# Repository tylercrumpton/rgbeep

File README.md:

# rgbeep
An ESP-powered RGB-lit jumbo button using APA102 LEDs.

![pcb-top]![pcb-bottom]

## Overview
The **RGBeep** is a large, colorful WiFi button made using the parts from an off-the-shelf "tap light".
It was inspired by [todbot's CrashSpace BigButton][todbot] that uses the same components. I loved the design,
but wanted to use APA102 RGB LEDs instead WS2182s, remove the "sacrificial Neopixel", and play with the mechanics a little bit.

On board, there are 16 APA102 SPI-controllable RGB LEDs, four pushbuttons, and a socket for either a Wemos D1 Mini ESP8266 module
or a [Synapse-powered S1 Mini][s1].

The diffuser insert is optional, but helps to hide the pixels underneath the dome. It is meant to be installed between 
the PCB and the dome with the "fins" oriented downwards, torward the PCB. White filament is recommended. 
The model was designed/printed/tested with an FDM printer at .2mm layer height.

## Operation
The **RGBeep**'s D1 Mini or S1 Mini module communicate with the APA102 LEDs via SPI, and the pushbuttons are connected to GPIO pins.
The pin mappings are as follows:

| Description | Module Pin |
|-------------|------------|
| APA102 CLK  | D5         |
| APA102 DATA | D7         |
| Switch SW1  | D1         |
| Switch SW2  | D2         |
| Switch SW3  | D3         |
| Switch SW4  | D4         |

[pcb-top]: https://cloud.githubusercontent.com/assets/1317406/22604399/045c0e30-ea11-11e6-9dd1-bee5b901c55e.png
[pcb-bottom]: https://cloud.githubusercontent.com/assets/1317406/22604385/fb816bde-ea10-11e6-9f9d-aa37f6f3053a.png
[todbot]: https://todbot.com/blog/2017/01/12/crashspace-bigbutton-w-esp8266/
[s1]: https://github.com/tylercrumpton/s1-mini

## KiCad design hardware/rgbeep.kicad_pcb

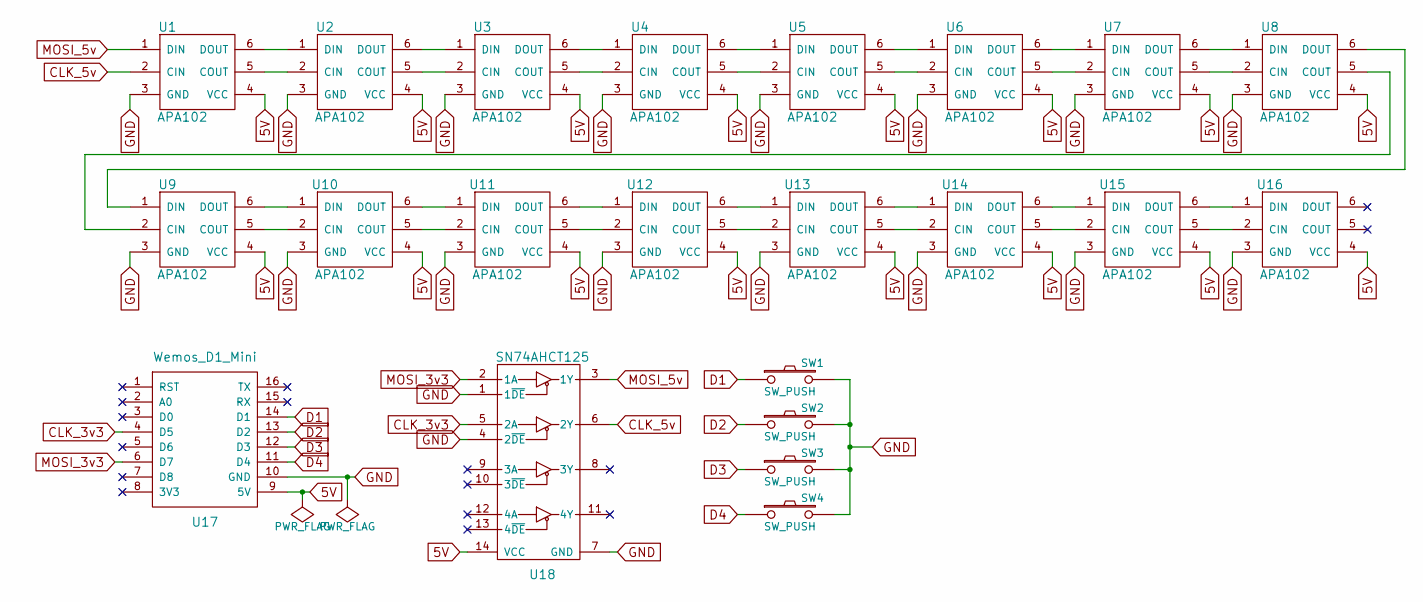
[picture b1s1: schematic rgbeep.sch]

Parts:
SW1, SW2, SW3, SW4: SW_PUSH; 6x6mm_pushbutton
U1, U2, U3, U4, U5, U6, U7, U8, U9, U10, U11, U12, U13, U14, U15, U16: APA102
U17: Wemos_D1_Mini; D1_mini
U18: SN74AHCT125; SOIC-14_3.9x8.7mm_Pitch1.27mm

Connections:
5V: U1.4 (VCC), U2.4 (VCC), U3.4 (VCC), U4.4 (VCC), U5.4 (VCC), U6.4 (VCC), U7.4 (VCC), U8.4 (VCC), U9.4 (VCC), U10.4 (VCC), U11.4 (VCC), U12.4 (VCC), U13.4 (VCC), U14.4 (VCC), U15.4 (VCC), U16.4 (VCC), U17.9 (5V), U18.14 (VCC)
CLK_3v3: U17.4 (D5), U18.5 (2A)
CLK_5v: U1.2 (CIN), U18.6 (2Y)
D1: SW1.1, U17.14 (D1)
D2: SW2.1, U17.13 (D2)
D3: SW3.1, U17.12 (D3)
D4: SW4.1, U17.11 (D4)
GND: SW1.2, SW2.2, SW3.2, SW4.2, U1.3 (GND), U2.3 (GND), U3.3 (GND), U4.3 (GND), U5.3 (GND), U6.3 (GND), U7.3 (GND), U8.3 (GND), U9.3 (GND), U10.3 (GND), U11.3 (GND), U12.3 (GND), U13.3 (GND), U14.3 (GND), U15.3 (GND), U16.3 (GND), U17.10 (GND), U18.1 (1~DE), U18.4 (2~DE), U18.7 (GND)
MOSI_3v3: U17.6 (D7), U18.2 (1A)
MOSI_5v: U1.1 (DIN), U18.3 (1Y)
unnamed: U1.5 (COUT), U2.2 (CIN)
unnamed: U1.6 (DOUT), U2.1 (DIN)
unnamed: U2.5 (COUT), U3.2 (CIN)
unnamed: U2.6 (DOUT), U3.1 (DIN)
unnamed: U3.5 (COUT), U4.2 (CIN)
unnamed: U3.6 (DOUT), U4.1 (DIN)
unnamed: U4.5 (COUT), U5.2 (CIN)
unnamed: U4.6 (DOUT), U5.1 (DIN)
unnamed: U5.5 (COUT), U6.2 (CIN)
unnamed: U5.6 (DOUT), U6.1 (DIN)
unnamed: U6.5 (COUT), U7.2 (CIN)
unnamed: U6.6 (DOUT), U7.1 (DIN)
unnamed: U7.5 (COUT), U8.2 (CIN)
unnamed: U7.6 (DOUT), U8.1 (DIN)
unnamed: U8.5 (COUT), U9.2 (CIN)
unnamed: U8.6 (DOUT), U9.1 (DIN)
unnamed: U9.6 (DOUT), U10.1 (DIN)
unnamed: U9.5 (COUT), U10.2 (CIN)
unnamed: U10.5 (COUT), U11.2 (CIN)
unnamed: U10.6 (DOUT), U11.1 (DIN)
unnamed: U11.5 (COUT), U12.2 (CIN)
unnamed: U11.6 (DOUT), U12.1 (DIN)
unnamed: U12.5 (COUT), U13.2 (CIN)
unnamed: U12.6 (DOUT), U13.1 (DIN)
unnamed: U13.5 (COUT), U14.2 (CIN)
unnamed: U13.6 (DOUT), U14.1 (DIN)
unnamed: U14.5 (COUT), U15.2 (CIN)
unnamed: U14.6 (DOUT), U15.1 (DIN)
unnamed: U15.5 (COUT), U16.2 (CIN)
unnamed: U15.6 (DOUT), U16.1 (DIN)

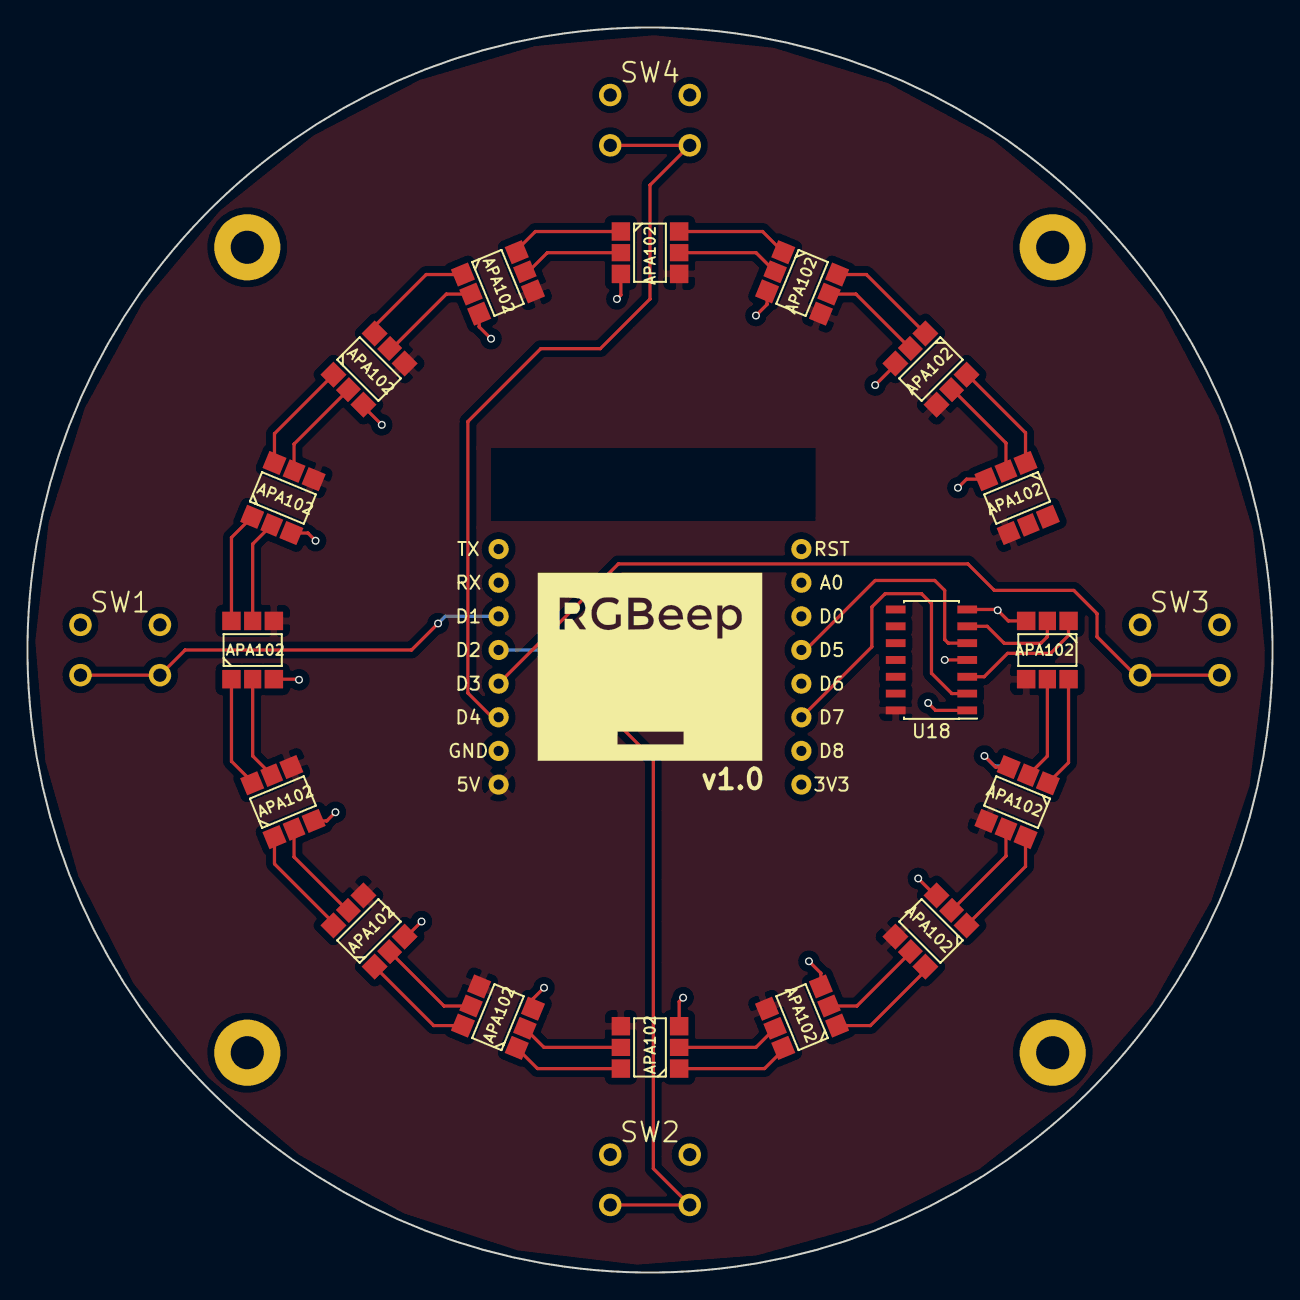
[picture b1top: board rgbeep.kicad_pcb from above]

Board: 2 copper layers, 94.0 x 94.0 mm, 22 parts (1 on the bottom side), 40 nets.

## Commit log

2017-01-29 Add KiCad project template.
2017-01-29 Update CrumpSchemes to get level shifter.
2017-01-29 Add schematic capture.
2017-01-29 Select footprints for parts.
2017-02-01 Route v1.0 board.
2017-02-03 Set plot settings.
2017-02-08 Add all the info to README.
2017-03-02 Fix DATA pin number.
2019-12-22 3D printable LED diffuser insert f3d and stl files plus README notes

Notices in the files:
hardware/rgbeep.kicad_pcb:
CC-BY-SA 4.0
